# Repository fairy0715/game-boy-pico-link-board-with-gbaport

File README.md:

# USB TO GAMEBOY LINK CABLE ADAPTER

フォーク元の基板にGBA用通信ポートを追加しました、基板を傷めずに接続できます。  
以下はフォーク元のREADMEを追記・修正して作成しています

ライセンスは自作した[libraries/gba_linkport Libraries](libraries/gba_linkport%20Libraries)内のみ[CC0](http://creativecommons.org/publicdomain/zero/1.0/deed.ja)です。  
その他はMITライセンスを引き継いでいます。

Raspberry Pi Pico用のオープンソースUSB-ゲームボーイリンクケーブルアダプタです。入手しやすくはんだ付けしやすい部品で設計されています。

stacksmashing の Gameboy Link adapter に基づいています: https://www.youtube.com/watch?v=KtHu693wE9o

## 回路図

## 部品

|リファレンス|型番|説明|
|---|---|---|
|U1|[Raspberry Pi Pico](https://www.raspberrypi.com/products/raspberry-pi-pico/)|クローン品も互換性あり|
|U2|BOB-12009 [sparkfun](https://www.sparkfun.com/products/12009) [秋月電子（未検証）](https://akizukidenshi.com/catalog/g/g113837/)|Sparkfun 双方向ロジックコンバータ（クローン品も互換性あり）|
|SW1|SS12D00-G3 [amazon](https://www.amazon.com/Tnuocke-Vertical-Position-Switches-SS12D00-G3/dp/B099MRCDG8) [秋月電子](https://akizukidenshi.com/catalog/g/g115707/)|1回路2接点 2.54mmピッチ スライドスイッチ|

SW1 はピンヘッダとジャンパで代用できます

|リファレンス|型番|説明|
|---|---|---|
|SW1|[ピンヘッダ](https://www.amazon.com/dp/B07PKKY8BX)|1x3 2.54mm オスピンヘッダー|
|-|[ジャンパ](https://www.amazon.com/dp/B077957RN7)|2.54mm ジャンパピン、古いマザーボードまたはハードドライブから取り出してください|

添付のリンクは参考用です。同等の部品であればどれでも使用できます。  
秋月電子のレベルシフタは、部品実装面が基板側に来るように配置が必要だと思います。

[テスト済み部品一覧](COMPONENTS.md)

## 基板の注文

基板のデータはリリース内の`gerbers.zip`を使用するか、Kicadファイルから生成してください。[JLCPCB](https://jlcpcb.com/)や[PCBWay](https://www.pcbway.com/)などで注文できます。

ソルダーマスクとシルクスクリーンの色は自由です。  
以下はGBAコネクタを使用せず、直接基板に通信ケーブルを繋ぐ場合の注意点です。

- 基板の厚みは 1.2mm を指定
- 表面処理は ENIG（金メッキ）を推奨

## 基板の組み立て

1. ヤスリなどを使って、基板上のコネクタ部の幅を適切なサイズにカットする
1. Raspberry Pi Picoとレベルシフタモジュールを基板にはんだ付けする（適宜ピンヘッダを使用する）
1. ニッパーで余分なピンを切り落とす
1. スイッチ or ピンヘッダ+ジャンパをはんだ付けする
1. Raspberry Pi Picoにファームウェアを書き込む（[互換性](#互換性) を参照）

## 使い方

GB/GBCソフトの場合はジャンパピンをDMG/GBC側に、GBAソフトの場合はジャンパピンをGBA側に取り付けてください。

>[!WARNING]
>ゲームボーイ/ゲームボーイカラーモードは5Vロジックを使用し、ゲームボーイアドバンスモードは3.3Vロジックを使用することに注意してください。損傷を防ぐため、ジャンパが正しい側に接続されていることを確認してください。

その後 Raspberry Pi Pico を PC に接続し、通信ポート or 基板のコネクタとゲームボーイ（シリーズ）を通信ケーブルで接続してください。

## 互換性

この基板は以下のファームウェアと互換性があります。
- https://github.com/Lorenzooone/gb-link-firmware-reconfigurable （推奨ファームウェア）
- https://github.com/stacksmashing/gb-link-firmware
- https://github.com/stacksmashing/gb-link-printer
- https://github.com/Lorenzooone/PokemonGB_Online_Trades
- https://github.com/dj505/GBPrinterEmu
- https://github.com/Squaresweets/GBPrinter-discord-bot
- https://github.com/KuestenKeks/pc-to-gb-printer

若干の変更を加えることで、以下のような他のファームウェアとも互換性があるはずです。
- https://github.com/untoxa/pico-gb-printer

## 参考

- Raspberry Pi Pico Footprint: https://github.com/ncarandini/KiCad-RP-Pico
- Logic Level Converter (BOB-12009) Footprint: https://www.snapeda.com/parts/BOB-12009/SparkFun%20Electronics/view-part/
- Gameboy Link Connector Footprint: https://github.com/Palmr/gb-link-cable
- 1.2mm PCB Thickness, based on: https://hackaday.io/project/12932-game-link-online/log/43999-received-the-breakout-boards

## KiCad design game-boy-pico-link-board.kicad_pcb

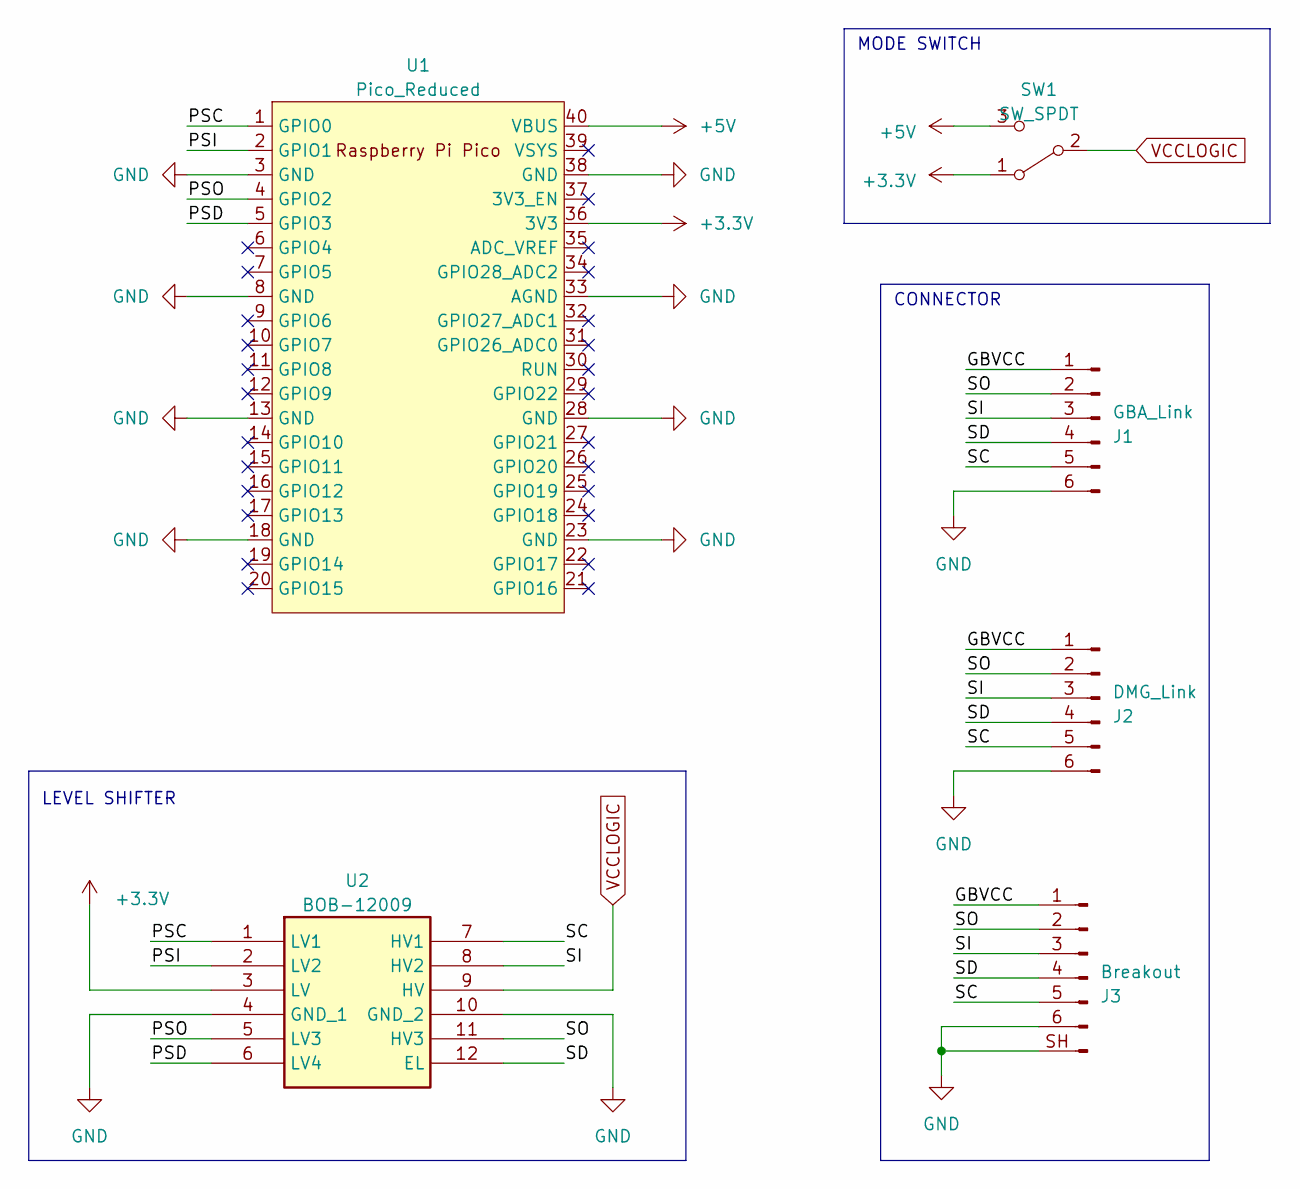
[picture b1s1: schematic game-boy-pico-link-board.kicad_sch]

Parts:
J1: GBA_Link; gb-link-socket
J2: DMG_Link; dmg-link-socket
J3: Breakout; gba_linkport
SW1: SW_SPDT; PinHeader_1x03_P2.54mm_Vertical
U1: Pico_Reduced; RPi_Pico_SMD_TH_REDUCED
U2: BOB-12009

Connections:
+3.3V: SW1.1 (A), U1.36 (3V3), U2.3 (LV)
+5V: SW1.3 (C), U1.40 (VBUS)
/GBVCC: J1.1, J2.1, J3.1
/PSC: U1.1 (GPIO0), U2.1 (LV1)
/PSD: U1.5 (GPIO3), U2.6 (LV4)
/PSI: U1.2 (GPIO1), U2.2 (LV2)
/PSO: U1.4 (GPIO2), U2.5 (LV3)
/SC: J1.5, J2.5, J3.5, U2.7 (HV1)
/SD: J1.4, J2.4, J3.4, U2.12 (EL)
/SI: J1.3, J2.3, J3.3, U2.8 (HV2)
/SO: J1.2, J2.2, J3.2, U2.11 (HV3)
GND: J1.6, J2.6, J3.6, J3.SH (Pin_7), U1.3 (GND), U1.8 (GND), U1.13 (GND), U1.18 (GND), U1.23 (GND), U1.28 (GND), U1.33 (AGND), U1.38 (GND), U2.4 (GND_1), U2.10 (GND_2)
VCCLOGIC: SW1.2 (B), U2.9 (HV)

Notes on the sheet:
LEVEL SHIFTER
MODE SWITCH
CONNECTOR

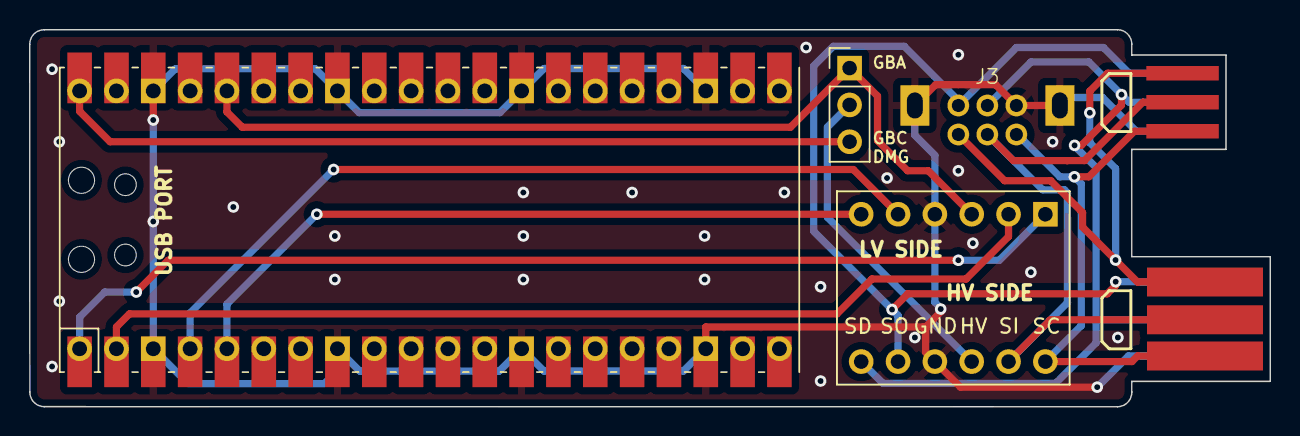
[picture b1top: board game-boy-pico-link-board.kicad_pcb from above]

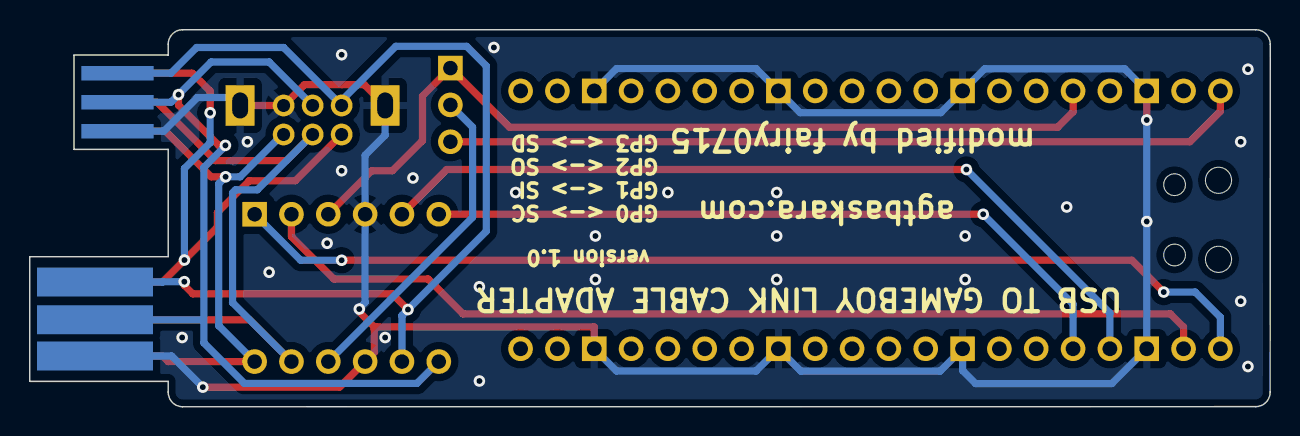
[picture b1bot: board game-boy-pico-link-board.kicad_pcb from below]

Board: 2 copper layers, 85.5 x 26.0 mm, 6 parts (2 on the bottom side), 13 nets.

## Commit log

2026-06-11 readmeを修正
2026-06-11 COMPONENTS.mdを翻訳・追記
